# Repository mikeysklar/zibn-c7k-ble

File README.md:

# zibn-c7k-ble
Chorded 7-Key BLE Desktop keyboard

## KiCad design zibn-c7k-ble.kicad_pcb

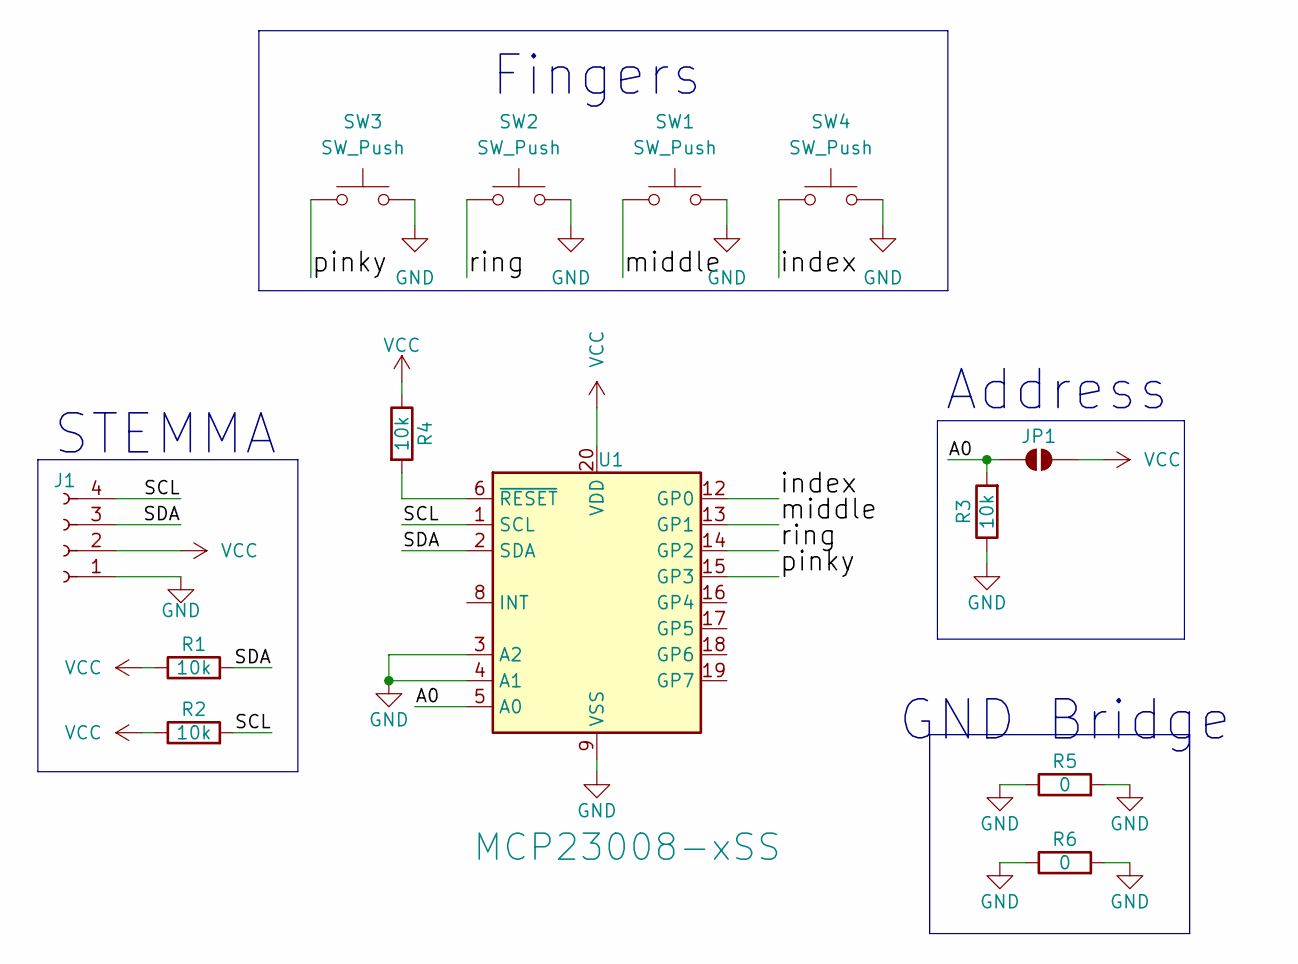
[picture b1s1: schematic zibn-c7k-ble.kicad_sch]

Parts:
J1: Conn_01x04_Socket; JST_SH_SM04B-SRSS-TB_1x04-1MP_P1.00mm_Horizontal
JP1: SolderJumper_2_Open; SolderJumper-2_P1.3mm_Open_TrianglePad1.0x1.5mm
R1, R2, R3, R4: 10k; R_0805_2012Metric_Pad1.20x1.40mm_HandSolder
R5, R6: 0; R_0805_2012Metric_Pad1.20x1.40mm_HandSolder
SW1, SW2, SW3, SW4: SW_Push; Kailh_socket_PG1350
U1: MCP23008-xSS; SSOP-20_5.3x7.2mm_P0.65mm

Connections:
/A0: JP1.1 (A), R3.2, U1.5 (A0)
/SCL: J1.4, R2.2, U1.1 (SCL)
/SDA: J1.3, R1.2, U1.2 (SDA)
/index: SW4.1, U1.12 (GP0)
/middle: SW1.1, U1.13 (GP1)
/pinky: SW3.1, U1.15 (GP3)
/ring: SW2.1, U1.14 (GP2)
GND: J1.1, R3.1, R5.1, R5.2, R6.1, R6.2, SW1.2, SW2.2, SW3.2, SW4.2, U1.3 (A2), U1.4 (A1), U1.9 (VSS)
unnamed: R4.2, U1.6 (~RESET)
VCC: J1.2, JP1.2 (B), R1.1, R2.1, R4.1, U1.20 (VDD)

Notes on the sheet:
GND Bridge
STEMMA
Fingers
Address

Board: 2 copper layers, 13 parts (0 on the bottom side), 10 nets, no tracks yet.

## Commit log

2025-05-17 sch / pcb check-in
